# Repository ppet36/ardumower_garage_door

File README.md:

# ArduMower electric garage door

This repository contains resources for my electric garage door for ArduMower. I created them because cats and other animals went to the garage and left the products of their digestive tract in it :)

Used motor is UXCELL 30RPM 24V motor (https://www.ebay.com/itm/DC-24V-30RPM-8mmx15mm-Dual-D-Shape-Shaft-Electric-Power-Turbo-Worm-Geared-Motor/362278845277).

Pad between two 100n capacitors is connected directly to the chassis of motor to avoid interference. PCB is mounted on motor with four M4 screws.

Extra space (top/left) around motor is used for mounting micro-switches at desired position.

Door in the action can be seen on YouTube https://youtu.be/0yKCrzkIeTo

Signal pin is connected to perimeter sender. When sender is ON (mower is mowing) door is open. If mower is in garage eq. charging and perimeter sender is OFF, door is closed. Signal is connected on pin D10 a firmware of perimeter sender slightly modified to control pin.

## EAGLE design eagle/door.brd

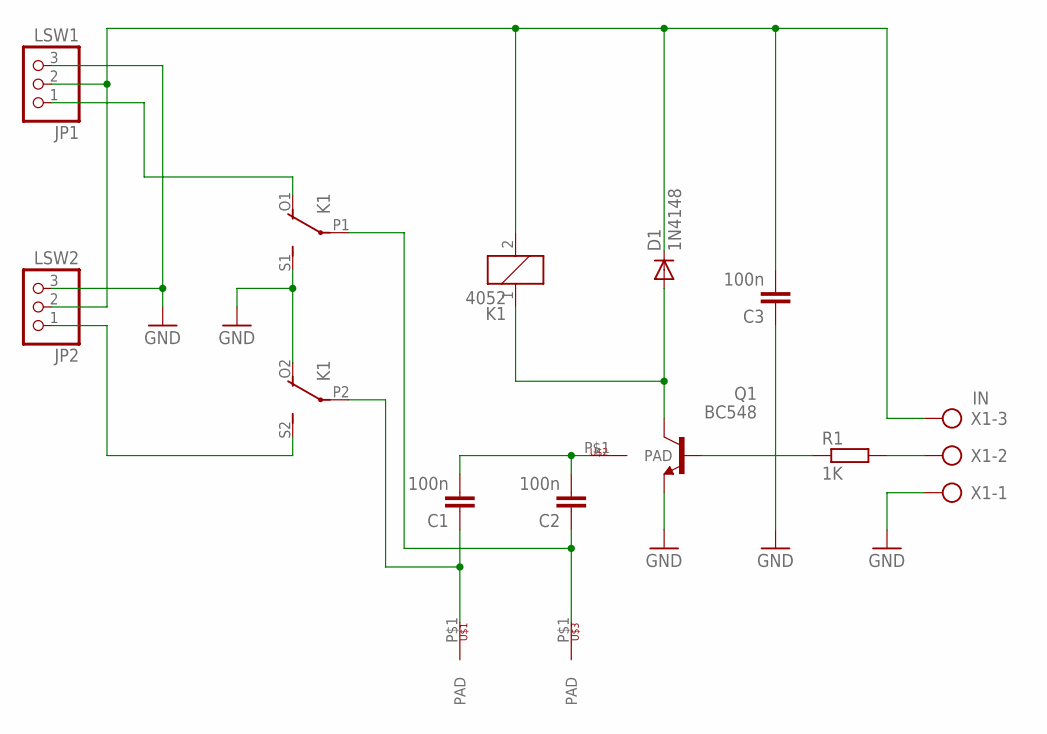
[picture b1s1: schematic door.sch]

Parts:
C1, C2, C3: 100n; C050-025X075
D1: 1N4148; DO35-7
JP1: LSW1; 1X03
JP2: LSW2; 1X03
K1: 4052; F4052
Q1: BC548; TO92-EBC
R1: 1K; 0204/7
U$1, U$2, U$3: PAD
X1: IN; AK300/3

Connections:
+24VDC: C3.2, D1.C, JP1.2, JP2.2, K1.2, X1.3
DRIVE: R1.2, X1.2
GND: C3.1, JP1.3, JP2.3, K1.O2 (O), K1.S1 (S), Q1.E, X1.1
unnamed: D1.A, K1.1, Q1.C
unnamed: Q1.B, R1.1
unnamed: JP2.1, K1.S2 (S)
unnamed: C2.1, K1.P1, U$3.P$1
unnamed: C1.1, K1.P2, U$1.P$1
unnamed: C1.2, C2.2, U$2.P$1
unnamed: JP1.1, K1.O1 (O)

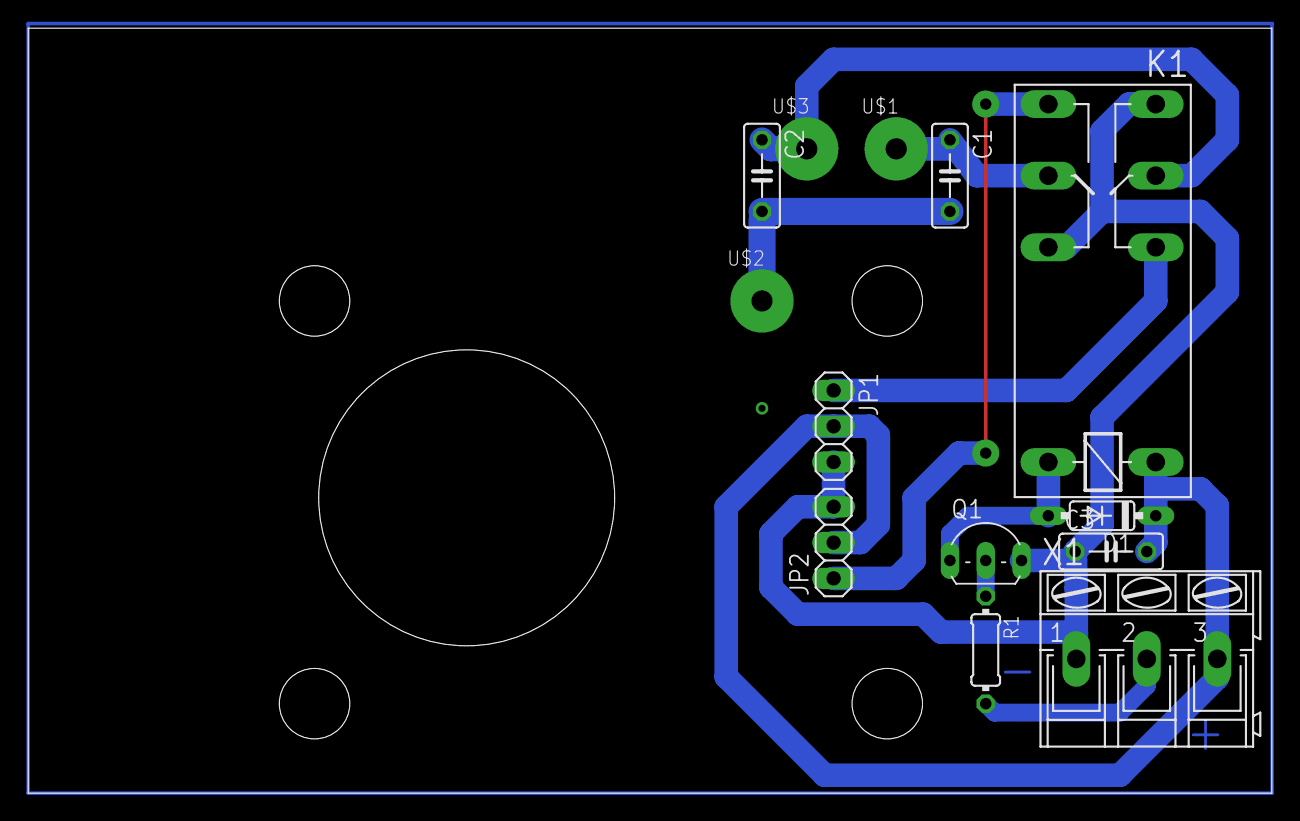
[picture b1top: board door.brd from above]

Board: 2 copper layers, 88.2 x 54.3 mm, 13 parts (0 on the bottom side), 10 nets.
